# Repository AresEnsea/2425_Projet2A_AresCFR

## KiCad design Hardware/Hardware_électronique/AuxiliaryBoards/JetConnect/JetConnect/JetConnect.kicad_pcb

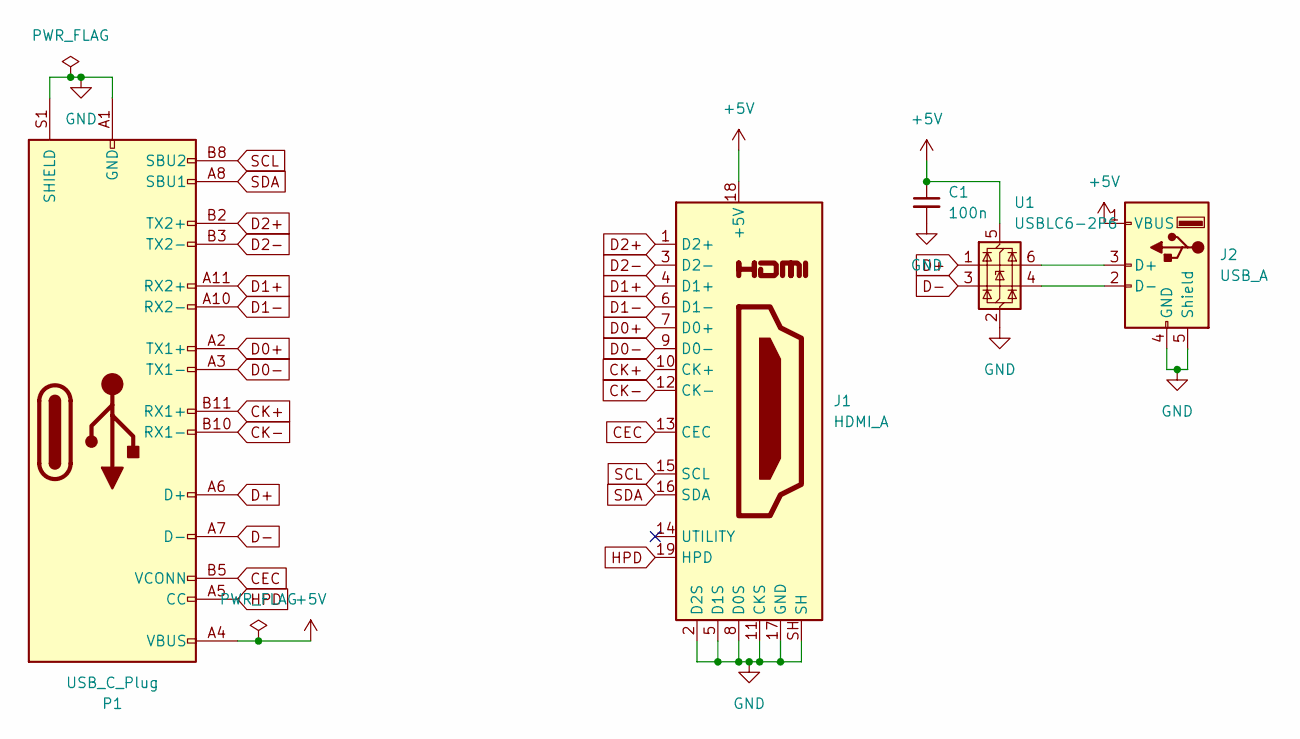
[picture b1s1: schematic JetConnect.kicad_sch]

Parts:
C1: 100n; C_0603_1608Metric_Pad1.08x0.95mm_HandSolder
J1: HDMI_A; HDMI_A_Amphenol_10029449-x01xLF_Horizontal
J2: USB_A; USB_A_Molex_67643_Horizontal
P1: USB_C_Plug; USB_C_Receptacle_CNCTech_C-ARA1-AK51X
U1: USBLC6-2P6; SOT-666

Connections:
+5V: C1.1, J1.18 (+5V), J2.1 (VBUS), P1.A4 (VBUS), P1.A9 (VBUS), P1.B4 (VBUS), P1.B9 (VBUS), U1.5 (VBUS)
CEC: J1.13 (CEC), P1.B5 (VCONN)
CK+: J1.10 (CK+), P1.B11 (RX1+)
CK-: J1.12 (CK-), P1.B10 (RX1-)
D0+: J1.7 (D0+), P1.A2 (TX1+)
D0-: J1.9 (D0-), P1.A3 (TX1-)
D1+: J1.4 (D1+), P1.A11 (RX2+)
D1-: J1.6 (D1-), P1.A10 (RX2-)
D2+: J1.1 (D2+), P1.B2 (TX2+)
D2-: J1.3 (D2-), P1.B3 (TX2-)
D+: P1.A6 (D+), U1.1 (I/O1)
D-: P1.A7 (D-), U1.3 (I/O2)
GND: C1.2, J1.2 (D2S), J1.5 (D1S), J1.8 (D0S), J1.11 (CKS), J1.17 (GND), J1.SH, J2.4 (GND), J2.5 (Shield), P1.A1 (GND), P1.A12 (GND), P1.B1 (GND), P1.B12 (GND), P1.S1 (SHIELD), U1.2 (GND)
HPD: J1.19 (HPD), P1.A5 (CC)
unnamed: J2.3 (D+), U1.6 (I/O1)
unnamed: J2.2 (D-), U1.4 (I/O2)
SCL: J1.15 (SCL), P1.B8 (SBU2)
SDA: J1.16 (SDA), P1.A8 (SBU1)

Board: 2 copper layers, 5 parts (0 on the bottom side), 18 nets, no tracks yet.
